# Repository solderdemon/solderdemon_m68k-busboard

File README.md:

# SolderDemon m68k Busboard

## Overview

A SolderDemon m68k backplane with one host slot, four expansion slots, and selectable 5 V DC power inputs.

The expansion slots support [rosco_m68k](https://github.com/rosco-m68k/rosco_m68k) cards.

**Status.** r1 fabrication files are available.

## Start here

- [KiCad project](design/solderdemon_m68k-busboard.kicad_pro)
- [Schematic (PDF)](manufacturing/solderdemon_m68k-busboard-schematic.pdf)
- [Connecting the host and cards](#connecting-the-host-and-the-cards)
- [Gerbers and drill files](manufacturing/solderdemon_m68k-busboard-gerbers.zip)

## Board views

| Top | Bottom |
|:---:|:---:|
|  |  |

## Hardware

### Features

- **Slot Architecture:** 5 identical slots (`BUS1`–`BUS5`), 2×32 vertical pin headers (2.54 mm / 0.1" pitch), 29.21 mm slot pitch; every slot carries the full 64-pin main bus; pin 1 of each slot is marked with a silkscreen triangle. `BUS1` (labelled `HOST`; the others `SLOT 1`–`SLOT 4`) is the host slot: the 20 mm strip to its left is kept free of tall parts so the host's components can face outwards
- **Power Inputs:** 5V DC only, from one of, down the right-hand edge:
  - DC Barrel Jack (`J1`, center-positive)
  - 2-pin 2.54 mm terminal (`J2`, under the jack)
- **Source Selection:** one jumper cap on the 2×3 header `JP2` (`SOURCE`) picks the input — the `DC` or `TERM` row (the third row is unused). Only the selected input reaches the switch, so two adapters are never tied together. No diodes, no voltage drop
- **Power Switch:** NKK M2021SS1W01 DPST toggle (`SW1`, both poles in parallel) between the selected input and `VCC`
- **Input Protection:** 1.5KE6.8A unidirectional TVS (`D1`, DO-201AE) across `VCC` / `GND`: 5.8 V standoff, above 5.25 V, so it does not leak on a good supply; it clamps over-voltage and conducts on reversed polarity
- **Host Power Link:** through-hole 1×2 jumper header `JP1` (`PWR LINK`), lying across the line midway between `HOST` and `SLOT 1`, under `C2`. It joins the host slot's pin 2 (`VCC_HOST`) to the bus `VCC`. Remove the jumper to power the host from its own `J5` while this board powers the cards
- **Filtering & Status:** 470 µF bulk reservoir (`C1`, upright) at the top right with `LED1` below it, as on the 6502 busboard. One 100 nF capacitor per slot stands vertically exactly halfway between two slot centres (`C2`–`C5`), its upper pad level with the slots' pin 1; `C6` continues the same 29.21 mm rhythm half a pitch past `SLOT 4`. Each is fed straight along the pin-1 row from its slot's pin 2; `C2` is on `VCC_HOST`
- **Form Factor:** 185 × 99 mm 2-layer PCB, through-hole components; power connectors and switch on the right-hand end, away from the host
- **Mounting:** 8× M3 mounting holes (3.2 mm) with grounded pads, 5.08 mm in from the edges as on the 6502 busboard; the four middle holes sit on the same half-pitch lines as the capacitors, above `C3` and `C5` and below the slots

### Pinout

All five slots are wired 1:1 to the main bus:

| Pin | Signal | Description | Pin | Signal | Description |
|:---:|:---|:---|:---:|:---|:---|
| **1** | **A1** | Address bus bit 1 | **2** | **VCC** | +5V power rail |
| **3** | **A2** | Address bus bit 2 | **4** | **CPUCLK** | CPU system clock |
| **5** | **A3** | Address bus bit 3 | **6** | **GND** | System ground (0V) |
| **7** | **A4** | Address bus bit 4 | **8** | **VPA** | Valid Peripheral Address |
| **9** | **A5** | Address bus bit 5 | **10** | **E** | 6800-style E clock |
| **11** | **A6** | Address bus bit 6 | **12** | **VMA** | Valid Memory Address |
| **13** | **A7** | Address bus bit 7 | **14** | **IRQ3** | Active-low interrupt input on the SolderDemon m68k host |
| **15** | **A8** | Address bus bit 8 | **16** | **IOSEL** | I/O select |
| **17** | **A9** | Address bus bit 9 | **18** | **EXPSEL** | Expansion select |
| **19** | **A10** | Address bus bit 10 | **20** | **FC0** | CPU function code 0 |
| **21** | **A11** | Address bus bit 11 | **22** | **FC1** | CPU function code 1 |
| **23** | **A12** | Address bus bit 12 | **24** | **FC2** | CPU function code 2 |
| **25** | **A13** | Address bus bit 13 | **26** | **IPL0** | Interrupt priority level 0 |
| **27** | **A14** | Address bus bit 14 | **28** | **IPL1** | Interrupt priority level 1 |
| **29** | **A15** | Address bus bit 15 | **30** | **IPL2** | Interrupt priority level 2 |
| **31** | **A16** | Address bus bit 16 | **32** | **LDS** | Lower Data Strobe |
| **33** | **A17** | Address bus bit 17 | **34** | **UDS** | Upper Data Strobe |
| **35** | **A18** | Address bus bit 18 | **36** | **RESET** | System reset |
| **37** | **A19** | Address bus bit 19 | **38** | **D15** | Data bus bit 15 |
| **39** | **A20** | Address bus bit 20 | **40** | **D14** | Data bus bit 14 |
| **41** | **A21** | Address bus bit 21 | **42** | **D13** | Data bus bit 13 |
| **43** | **A22** | Address bus bit 22 | **44** | **D12** | Data bus bit 12 |
| **45** | **A23** | Address bus bit 23 | **46** | **D11** | Data bus bit 11 |
| **47** | **AS** | Address Strobe | **48** | **D10** | Data bus bit 10 |
| **49** | **BERR** | Bus Error | **50** | **D9** | Data bus bit 9 |
| **51** | **BG** | Bus Grant | **52** | **D8** | Data bus bit 8 |
| **53** | **BGACK** | Bus Grant Acknowledge | **54** | **D7** | Data bus bit 7 |
| **55** | **BR** | Bus Request | **56** | **D6** | Data bus bit 6 |
| **57** | **DTACK** | Data Transfer Acknowledge | **58** | **D5** | Data bus bit 5 |
| **59** | **R/W** | Read / Write | **60** | **D4** | Data bus bit 4 |
| **61** | **D0** | Data bus bit 0 | **62** | **D3** | Data bus bit 3 |
| **63** | **D1** | Data bus bit 1 | **64** | **D2** | Data bus bit 2 |

#### Connecting the host and the cards

- **Host board in `BUS1`.** Fit a **right-angle 2×32 socket on the bottom side** of the `solderdemon_m68k` board in the J3 holes, body overhanging the left edge, instead of the vertical header. The host then stands in `BUS1` with its component side facing outwards (left), all its connectors reachable, pins matched 1:1. The socket must be on the bottom side: on the top side the pin order along the row comes out reversed. The host sits about 2 mm lower than the cards because J3 is 5.45 mm from the board edge; its tallest parts reach roughly the left edge of this board.
- **Host on a cable.** With the stock vertical header on J3 the host can instead hang off a 64-way IDC ribbon cable with a socket at both ends, plugged into any slot. The cable is wired 1:1; keep it short (under about 20 cm) because the bus is unbuffered and has a single GND line. Neither header is keyed: match the cable's pin 1 (red stripe) to the triangle on the slot and to pin 1 on J3, otherwise the bus board's own 5V lands on the CPU data lines.
- **Cards.** Expansion cards use a right-angle 2×32 socket on the component side of their right edge, pin 1 at the bottom. Plugged in, every card stands with its components facing left, towards the host slot, so cards look at the back of their left-hand neighbour and the `BUS5` card turns its back to the power section. A card inserted the other way round gets `VCC` on a data line, so check the triangle before powering up.
- **One power source.** With `JP1` fitted, the host's 5V rail is the bus `VCC`: power the system from this board only. To power the host from its own `J5` (for example during bring-up), take `JP1` off — the cards still run from this board, the host from its own supply.

#### Power Interfaces & Control

| Designator | Label | Type / Footprint | Description |
|:---|:---|:---|:---|
| **J1** | DC 5V ONLY | Barrel jack 5.5 / 2.1 mm | 5V DC input (center-positive, polarity symbol on the silkscreen) |
| **J2** | GND / +5V | Pin header 1×2, 2.54 mm | 5V input for a power cable, pin 1 = +5V (`VIN_TERM`), pin 2 = GND |
| **JP2** | SOURCE | Pin header 2×3, 2.54 mm, one jumper cap | Source select: odd pins 1 terminal and 3 DC jack; pin 5 unused; even pins the common input |
| **SW1** | POWER | NKK M2021SS1W01, DPST toggle | Main power ON / OFF, both poles in parallel |
| **D1** | — | 1.5KE6.8A, DO-201AE (THT) | TVS protection diode across `VCC` / `GND` |
| **JP1** | PWR LINK | Pin header 1×2, 2.54 mm, jumper cap | Links the host slot's `VCC_HOST` to `VCC` (fitted by default) |
| **LED1** | — | LED 5 mm | PWR GOOD: `VCC` present |

> **5V only.** There is no voltage regulator on this board. Supply regulated 5V through the `J2` terminal or the barrel jack. If more than ~6.5V or reversed polarity is applied, `D1` starts conducting and shorts the input. There is no fuse, so this relies on the supply's own over-current protection — a supply without it can destroy `D1`.

> **One input at a time, by design.** `JP2` connects exactly one input to the switch; the others stay open even when plugged in.

## Using the board

See [Connecting the host and the cards](#connecting-the-host-and-the-cards) for connector orientation and the power link.

## Build and verification

### Verification

See [Design files](#design-files) for fabrication files and reports.

### Bill of Materials (BOM)

| Reference | Value | Package / Footprint | Notes |
|:---|:---|:---|:---|
| **BUS1–BUS5** | Conn_02x32 | Pin header 2×32, 2.54 mm, vertical | Bus slots |
| **J1** | Jack-DC | Barrel jack 5.5 / 2.1 mm, horizontal | 5V DC input |
| **J2** | 5V IN | Pin header 1×2, 2.54 mm, vertical | 5V terminal input |
| **JP1** | PWR LINK | Pin header 1×2, 2.54 mm + jumper cap | Host power link |
| **JP2** | SOURCE | Pin header 2×3, 2.54 mm + jumper cap | Source select |
| **SW1** | M2021SS1W01 | NKK M-series DPST ON-OFF toggle switch | Main power switch |
| **D1** | 1.5KE6.8A | DO-201AE, Axial P15.24 mm (THT) | Unidirectional TVS diode |
| **LED1** | LED 5 mm | Radial D5.0 mm (THT) | PWR GOOD indicator |
| **C1** | 470 µF | Radial electrolytic, D10 mm, P3.5 mm, upright | Bulk reservoir capacitor |
| **C2–C6** | 100 nF | Radial ceramic, 5.08 mm lead pitch | One per slot (`C2`: host, on `VCC_HOST`) |
| **R1** | 1 kΩ | Axial DIN0207, P10.16 mm | LED1 current-limiting resistor |
| **H1–H8** | Mounting Hole | 3.2 mm M3, GND pad | Mounting holes |
| **LOGO1** | SolderDemon logo | Silkscreen only | Board-only graphic, not in the BOM |

Machine-readable BOM: [solderdemon_m68k-busboard-bom.csv](design/solderdemon_m68k-busboard-bom.csv).

### Design files

- **KiCad Project (KiCad 10):** `design/solderdemon_m68k-busboard.kicad_pro`, `design/solderdemon_m68k-busboard.kicad_sch`, `design/solderdemon_m68k-busboard.kicad_pcb`
- **How r1 is made:** `tools/build_sch.py` generates the schematic and BOM; `tools/standard_pcb.py` rebuilds from the routed bus at git `3a0c432`, brings over the 6502 power circuit and applies the revised placement and routing; `../tools/brand/apply_identity.py solderdemon_m68k-busboard` draws the shared labels and identity
- **Footprint Library:** `solderdemon_m68k-busboard.pretty/` (bus header, capacitor, resistor and power switch footprints, SolderDemon logo)
- **Logo:** the shared SolderDemon logo from `../tools/brand/` (library `SolderDemonBrand`)
- **Schematic PDF:** [solderdemon_m68k-busboard.pdf](solderdemon_m68k-busboard.pdf)
- **Fabrication files:** [manufacturing/](manufacturing/)
- **PCB Specs:** 2-layer board, 185 × 99 mm, 1.6 mm thickness, standard 1 oz copper, HASL / ENIG finish
- **Design Verification:** [DRC Report](solderdemon_m68k-busboard-drc.rpt) (0 violations, 0 unconnected, 0 schematic parity issues), [ERC Report](solderdemon_m68k-busboard-erc.rpt) (0 violations)

<!-- repository-layout -->
## Repository layout

- [`design/`](design/solderdemon_m68k-busboard.kicad_pro): KiCad project, schematic sheets, PCB, local libraries and design data. Open the project directly here.
- [`code/firmware/`](code/firmware/): ROM and programmable-logic sources and programming files.
- [`code/software/`](code/software/): drivers, examples and applications.
- [`code/build/`](code/build/): local build products; ignored by Git except for its README.
- [`tools/`](tools/): generators, simulations and export scripts. Run commands from the repository root unless stated otherwise.
- [`manufacturing/`](manufacturing/): fabrication packages.

This passive busboard has no firmware or software; the code directories document that explicitly.
Design files and documentation are generated by scripts in `tools/`; change the sources and regenerate. Keep `.kicad_pro` as the source of DRC rules.
<!-- /repository-layout -->

## Licences and attribution

Copyright © 2026 SolderDemon.

- **Hardware** — [CERN Open Hardware Licence v1.2](LICENCE.hardware.txt).

The SolderDemon r1 revision builds on the roscbus-01 backplane, © 2020 Ross Bamford & Contributors.

Third-party materials retain their original notices and licence terms.

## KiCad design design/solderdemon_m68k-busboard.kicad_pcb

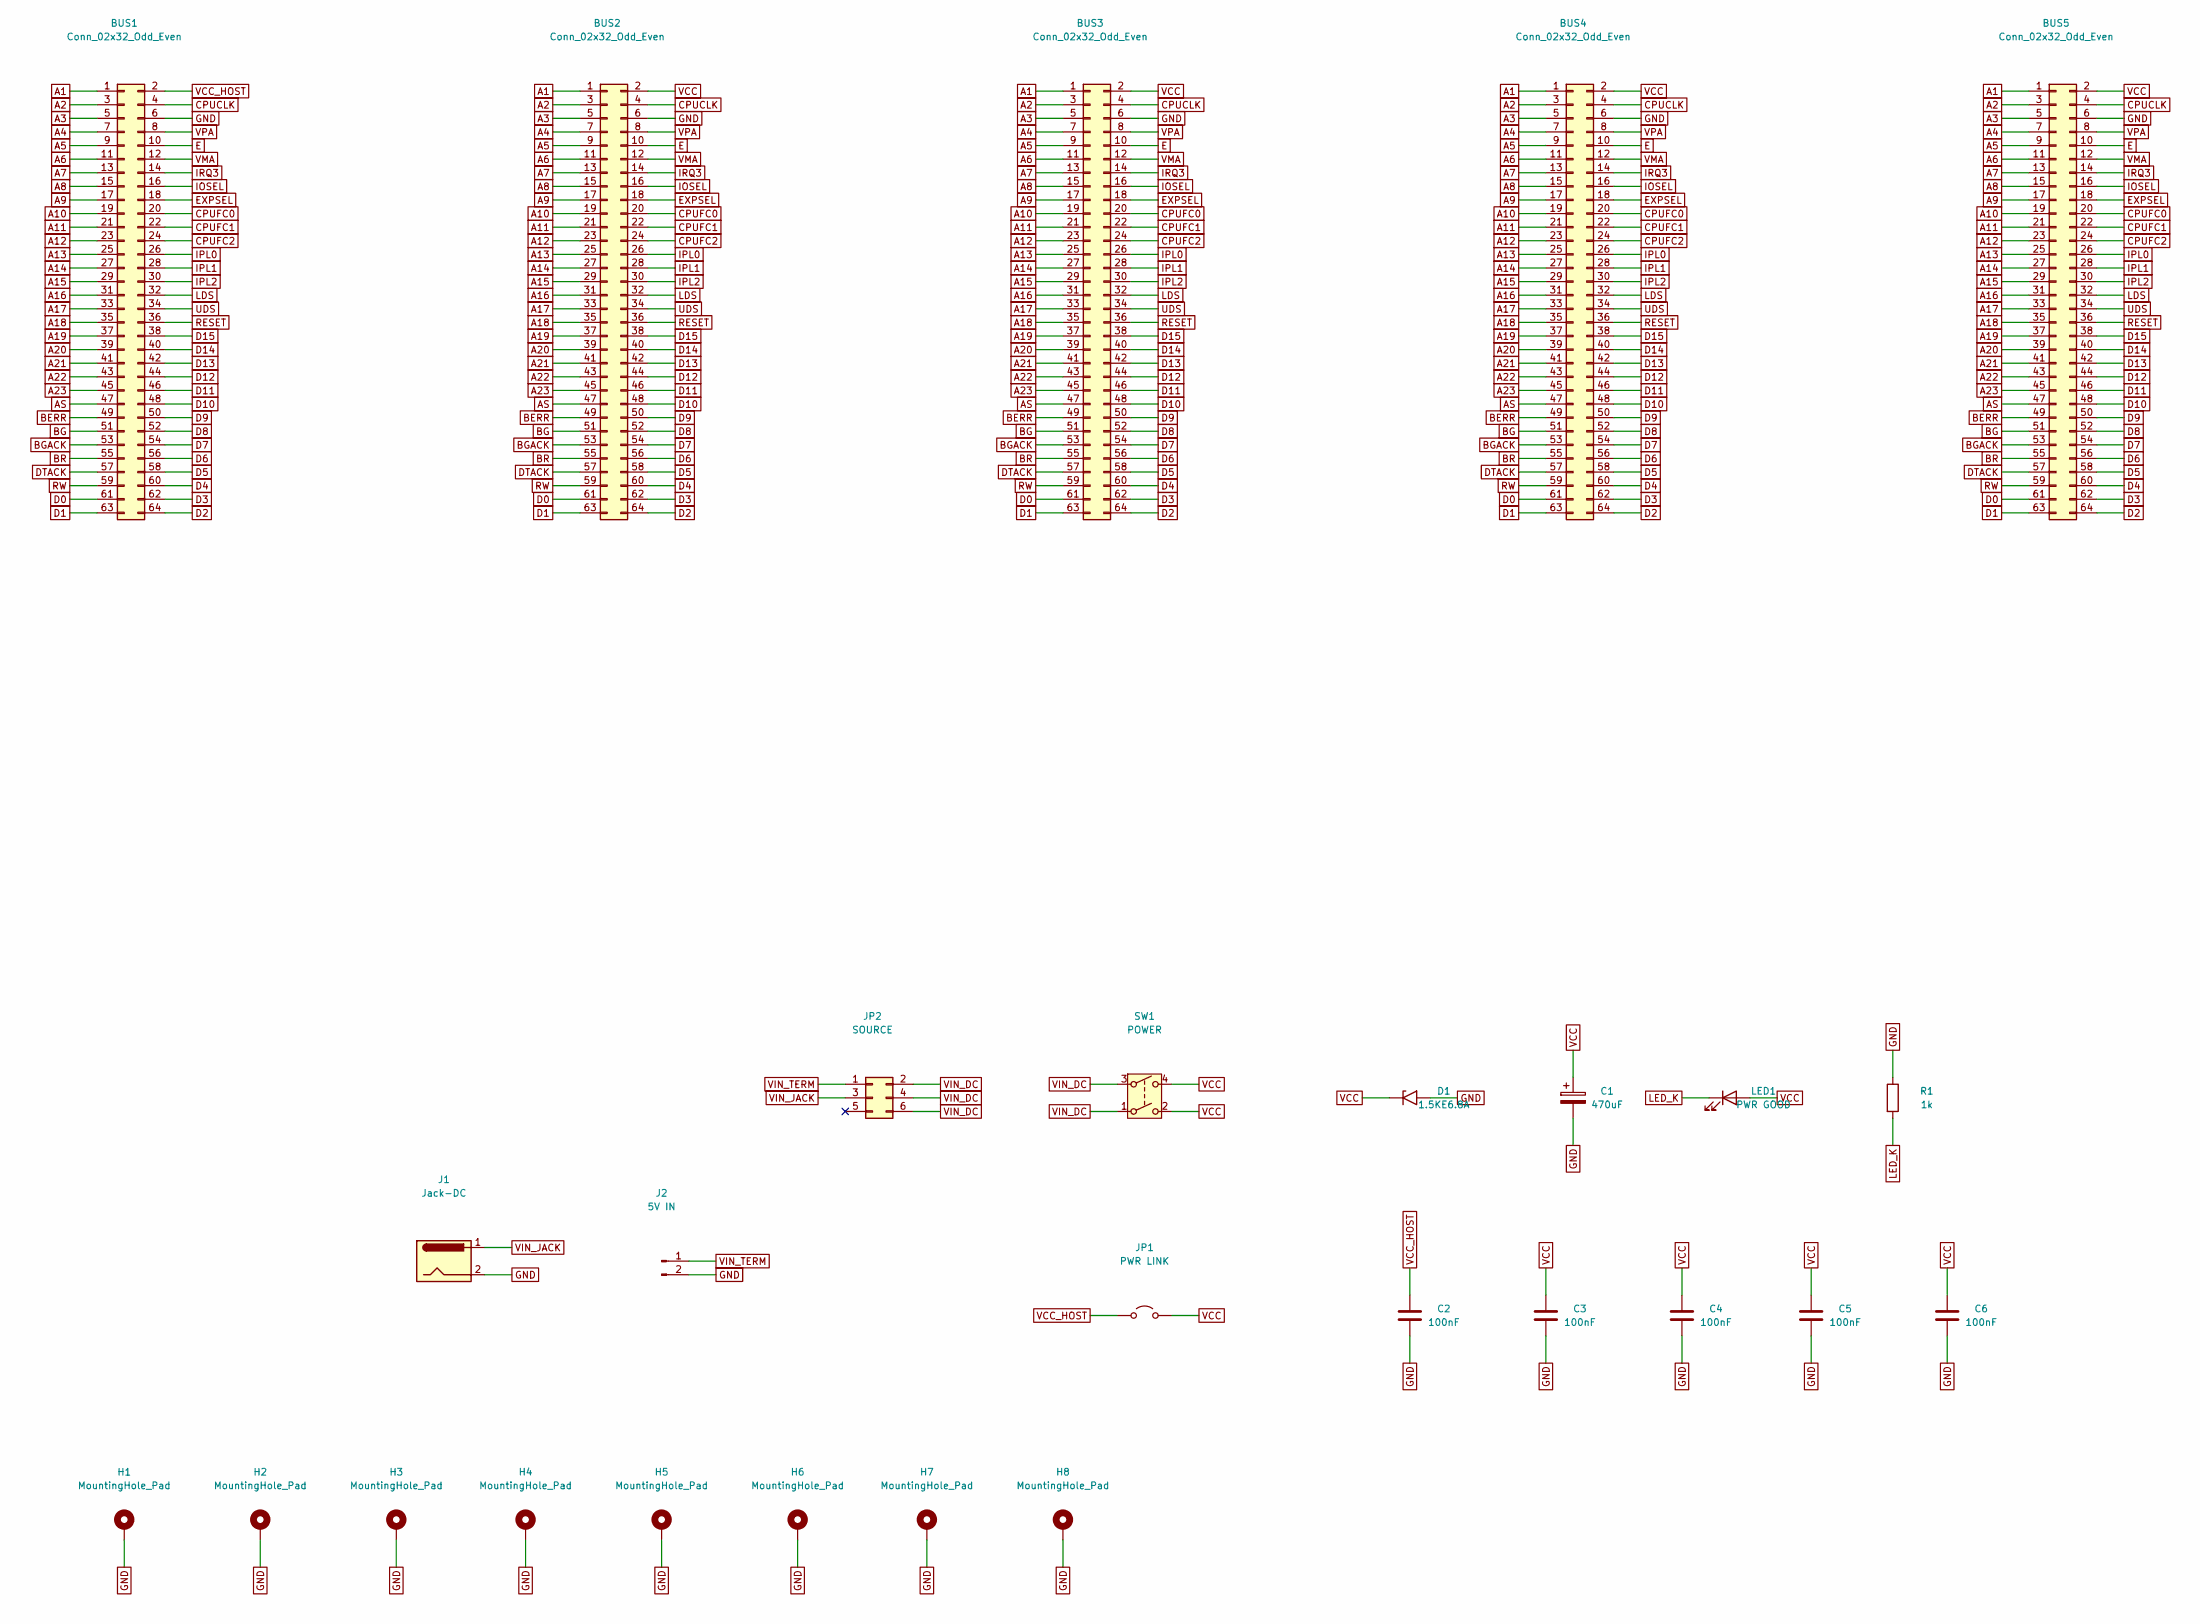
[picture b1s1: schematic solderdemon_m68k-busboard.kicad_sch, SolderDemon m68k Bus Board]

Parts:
BUS1, BUS2, BUS3, BUS4, BUS5: Conn_02x32_Odd_Even; pin-2X32
C1: 470uF; CP_Radial_D10.0mm_P3.50mm
C2, C3, C4, C5, C6: 100nF; C_Radial_5.08mm
D1: 1.5KE6.8A; D_DO-201AE_P15.24mm_Horizontal
H1, H2, H3, H4, H5, H6, H7, H8: MountingHole_Pad; MountingHole_3.2mm_M3_Pad
J1: Jack-DC; BarrelJack_Horizontal
J2: 5V IN; PinHeader_1x02_P2.54mm_Vertical
JP1: PWR LINK; PinHeader_1x02_P2.54mm_Vertical
JP2: SOURCE; PinHeader_2x03_P2.54mm_Vertical
LED1: PWR GOOD; LED_D5.0mm
R1: 1k; R_Axial_DIN0207_L6.3mm_D2.5mm_P10.16mm_Horizontal
SW1: POWER; NKK-M2021SS1W01

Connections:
A1: BUS1.1, BUS2.1, BUS3.1, BUS4.1, BUS5.1
A2: BUS1.3, BUS2.3, BUS3.3, BUS4.3, BUS5.3
A3: BUS1.5, BUS2.5, BUS3.5, BUS4.5, BUS5.5
A4: BUS1.7, BUS2.7, BUS3.7, BUS4.7, BUS5.7
A5: BUS1.9, BUS2.9, BUS3.9, BUS4.9, BUS5.9
A6: BUS1.11, BUS2.11, BUS3.11, BUS4.11, BUS5.11
A7: BUS1.13, BUS2.13, BUS3.13, BUS4.13, BUS5.13
A8: BUS1.15, BUS2.15, BUS3.15, BUS4.15, BUS5.15
A9: BUS1.17, BUS2.17, BUS3.17, BUS4.17, BUS5.17
A10: BUS1.19, BUS2.19, BUS3.19, BUS4.19, BUS5.19
A11: BUS1.21, BUS2.21, BUS3.21, BUS4.21, BUS5.21
A12: BUS1.23, BUS2.23, BUS3.23, BUS4.23, BUS5.23
A13: BUS1.25, BUS2.25, BUS3.25, BUS4.25, BUS5.25
A14: BUS1.27, BUS2.27, BUS3.27, BUS4.27, BUS5.27
A15: BUS1.29, BUS2.29, BUS3.29, BUS4.29, BUS5.29
A16: BUS1.31, BUS2.31, BUS3.31, BUS4.31, BUS5.31
A17: BUS1.33, BUS2.33, BUS3.33, BUS4.33, BUS5.33
A18: BUS1.35, BUS2.35, BUS3.35, BUS4.35, BUS5.35
A19: BUS1.37, BUS2.37, BUS3.37, BUS4.37, BUS5.37
A20: BUS1.39, BUS2.39, BUS3.39, BUS4.39, BUS5.39
A21: BUS1.41, BUS2.41, BUS3.41, BUS4.41, BUS5.41
A22: BUS1.43, BUS2.43, BUS3.43, BUS4.43, BUS5.43
A23: BUS1.45, BUS2.45, BUS3.45, BUS4.45, BUS5.45
AS: BUS1.47, BUS2.47, BUS3.47, BUS4.47, BUS5.47
BERR: BUS1.49, BUS2.49, BUS3.49, BUS4.49, BUS5.49
BG: BUS1.51, BUS2.51, BUS3.51, BUS4.51, BUS5.51
BGACK: BUS1.53, BUS2.53, BUS3.53, BUS4.53, BUS5.53
BR: BUS1.55, BUS2.55, BUS3.55, BUS4.55, BUS5.55
CPUCLK: BUS1.4, BUS2.4, BUS3.4, BUS4.4, BUS5.4
CPUFC0: BUS1.20, BUS2.20, BUS3.20, BUS4.20, BUS5.20
CPUFC1: BUS1.22, BUS2.22, BUS3.22, BUS4.22, BUS5.22
CPUFC2: BUS1.24, BUS2.24, BUS3.24, BUS4.24, BUS5.24
D0: BUS1.61, BUS2.61, BUS3.61, BUS4.61, BUS5.61
D1: BUS1.63, BUS2.63, BUS3.63, BUS4.63, BUS5.63
D2: BUS1.64, BUS2.64, BUS3.64, BUS4.64, BUS5.64
D3: BUS1.62, BUS2.62, BUS3.62, BUS4.62, BUS5.62
D4: BUS1.60, BUS2.60, BUS3.60, BUS4.60, BUS5.60
D5: BUS1.58, BUS2.58, BUS3.58, BUS4.58, BUS5.58
D6: BUS1.56, BUS2.56, BUS3.56, BUS4.56, BUS5.56
D7: BUS1.54, BUS2.54, BUS3.54, BUS4.54, BUS5.54
D8: BUS1.52, BUS2.52, BUS3.52, BUS4.52, BUS5.52
D9: BUS1.50, BUS2.50, BUS3.50, BUS4.50, BUS5.50
D10: BUS1.48, BUS2.48, BUS3.48, BUS4.48, BUS5.48
D11: BUS1.46, BUS2.46, BUS3.46, BUS4.46, BUS5.46
D12: BUS1.44, BUS2.44, BUS3.44, BUS4.44, BUS5.44
D13: BUS1.42, BUS2.42, BUS3.42, BUS4.42, BUS5.42
D14: BUS1.40, BUS2.40, BUS3.40, BUS4.40, BUS5.40
D15: BUS1.38, BUS2.38, BUS3.38, BUS4.38, BUS5.38
DTACK: BUS1.57, BUS2.57, BUS3.57, BUS4.57, BUS5.57
E: BUS1.10, BUS2.10, BUS3.10, BUS4.10, BUS5.10
EXPSEL: BUS1.18, BUS2.18, BUS3.18, BUS4.18, BUS5.18
GND: BUS1.6, BUS2.6, BUS3.6, BUS4.6, BUS5.6, C1.2, C2.2, C3.2, C4.2, C5.2, C6.2, D1.2 (A2), H1.1, H2.1, H3.1, H4.1, H5.1, H6.1, H7.1, H8.1, J1.2, J2.2, R1.1
IOSEL: BUS1.16, BUS2.16, BUS3.16, BUS4.16, BUS5.16
IPL0: BUS1.26, BUS2.26, BUS3.26, BUS4.26, BUS5.26
IPL1: BUS1.28, BUS2.28, BUS3.28, BUS4.28, BUS5.28
IPL2: BUS1.30, BUS2.30, BUS3.30, BUS4.30, BUS5.30
IRQ3: BUS1.14, BUS2.14, BUS3.14, BUS4.14, BUS5.14
LDS: BUS1.32, BUS2.32, BUS3.32, BUS4.32, BUS5.32
LED_K: LED1.1 (K), R1.2
RESET: BUS1.36, BUS2.36, BUS3.36, BUS4.36, BUS5.36
RW: BUS1.59, BUS2.59, BUS3.59, BUS4.59, BUS5.59
UDS: BUS1.34, BUS2.34, BUS3.34, BUS4.34, BUS5.34
VCC: BUS2.2, BUS3.2, BUS4.2, BUS5.2, C1.1, C3.1, C4.1, C5.1, C6.1, D1.1 (A1), JP1.2 (B), LED1.2 (A), SW1.2, SW1.4
VCC_HOST: BUS1.2, C2.1, JP1.1 (A)
VIN_DC: JP2.2, JP2.4, JP2.6, SW1.1, SW1.3
VIN_JACK: J1.1, JP2.3
VIN_TERM: J2.1, JP2.1
VMA: BUS1.12, BUS2.12, BUS3.12, BUS4.12, BUS5.12
VPA: BUS1.8, BUS2.8, BUS3.8, BUS4.8, BUS5.8

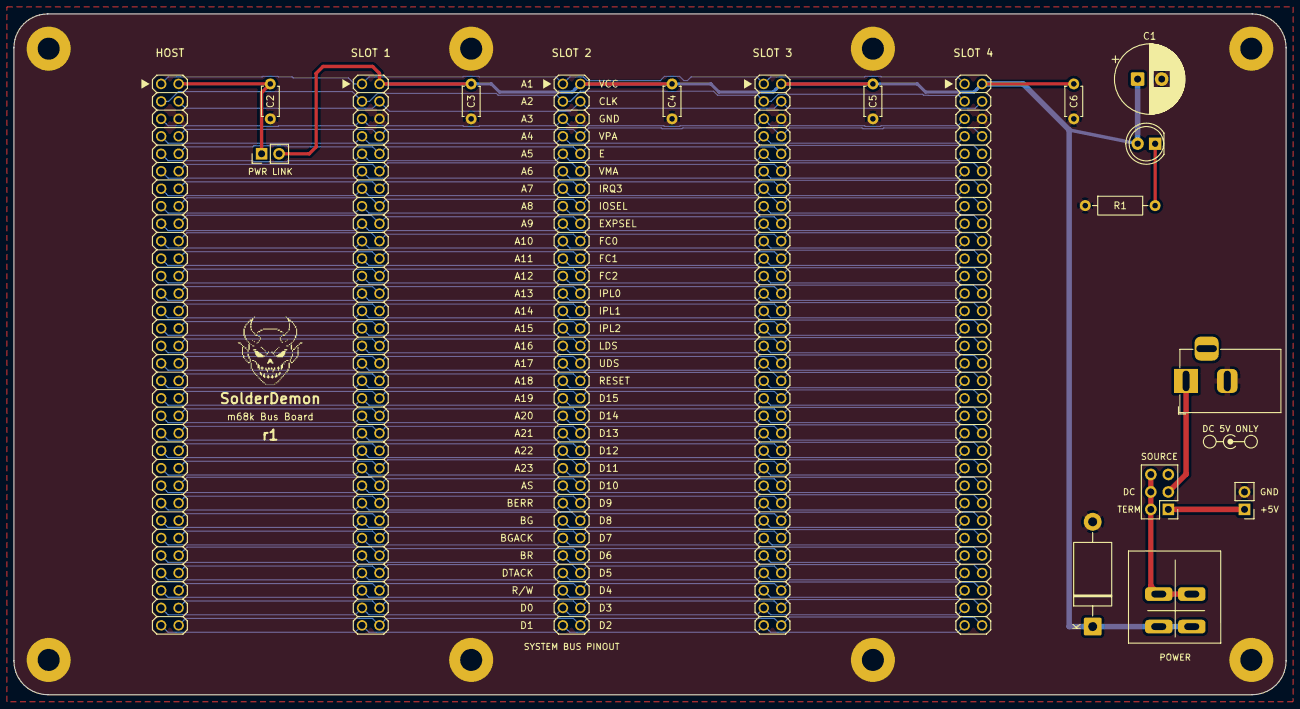
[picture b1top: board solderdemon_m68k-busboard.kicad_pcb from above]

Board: 2 copper layers, 185.0 x 99.0 mm, 28 parts (0 on the bottom side), 69 nets.

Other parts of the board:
LOGO1: SolderDemon_Logo
